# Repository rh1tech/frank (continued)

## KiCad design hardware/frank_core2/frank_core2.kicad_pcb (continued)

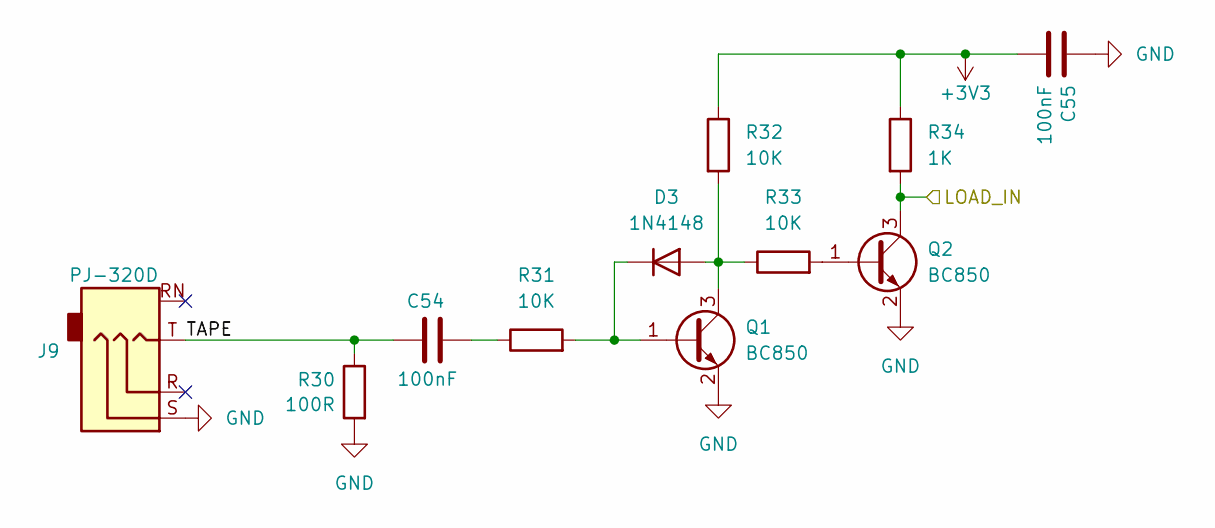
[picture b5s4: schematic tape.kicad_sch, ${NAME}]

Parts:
C54, C55: 100nF; C_0603_1608Metric; LCSC C14663
D3: 1N4148; D_SOD-323; LCSC C2128
J9: PJ-320D; AudioJack_3.5mm_PJ320D_TapeIn; LCSC C431535
Q1, Q2: BC850; SOT-23; LCSC C503377
R30: 100R; R_0603_1608Metric; LCSC C22775
R31, R32, R33: 10K; R_0603_1608Metric; LCSC C2906982
R34: 1K; R_0603_1608Metric; LCSC C21190

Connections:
+3V3: C55.2, R32.1, R34.1; also elsewhere on the board
/RP2350B/GPIO44: Q2.3 (C), R34.2; also elsewhere on the board
/Tape/TAPE: C54.1, J9.T, R30.1
GND: C55.1, J9.S, Q1.2 (E), Q2.2 (E), R30.2; also elsewhere on the board
unnamed: C54.2, R31.1
unnamed: D3.2 (A), Q1.3 (C), R32.2, R33.1
unnamed: D3.1 (K), Q1.1 (B), R31.2
unnamed: Q2.1 (B), R33.2

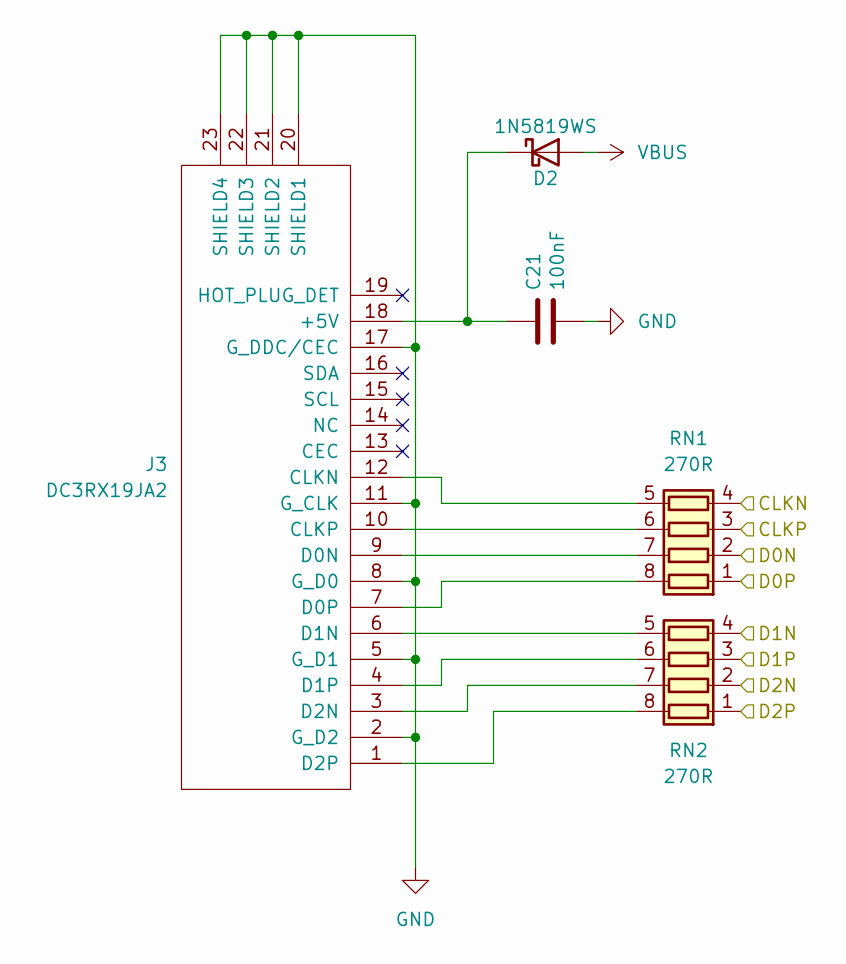
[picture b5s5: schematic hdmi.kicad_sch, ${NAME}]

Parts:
C21: 100nF; C_0603_1608Metric; LCSC C14663
D2: 1N5819WS; D_SOD-323; LCSC C191023
J3: DC3RX19JA2; HDMI_Female
RN1, RN2: 270R; R_Array_4x0603; LCSC C1731063

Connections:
/GPIO12/CLKN: RN1.4 (R4.1); also elsewhere on the board
/GPIO13/CLKP: RN1.3 (R3.1); also elsewhere on the board
/GPIO14/D0N: RN1.2 (R2.1); also elsewhere on the board
/GPIO15/D0P: RN1.1 (R1.1); also elsewhere on the board
/GPIO16/D1N: RN2.4 (R4.1); also elsewhere on the board
/GPIO17/D1P: RN2.3 (R3.1); also elsewhere on the board
/GPIO18/D2N: RN2.2 (R2.1); also elsewhere on the board
/GPIO19/D2P: RN2.1 (R1.1); also elsewhere on the board
GND: C21.2, J3.2 (G_D2), J3.5 (G_D1), J3.8 (G_D0), J3.11 (G_CLK), J3.17 (G_DDC/CEC), J3.20 (SHIELD1), J3.21 (SHIELD2), J3.22 (SHIELD3), J3.23 (SHIELD4); also elsewhere on the board
unnamed: C21.1, D2.1 (K), J3.18 (+5V)
unnamed: J3.12 (CLKN), RN1.5 (R4.2)
unnamed: J3.10 (CLKP), RN1.6 (R3.2)
unnamed: J3.9 (D0N), RN1.7 (R2.2)
unnamed: J3.7 (D0P), RN1.8 (R1.2)
unnamed: J3.6 (D1N), RN2.5 (R4.2)
unnamed: J3.4 (D1P), RN2.6 (R3.2)
unnamed: J3.3 (D2N), RN2.7 (R2.2)
unnamed: J3.1 (D2P), RN2.8 (R1.2)
VBUS: D2.2 (A); also elsewhere on the board

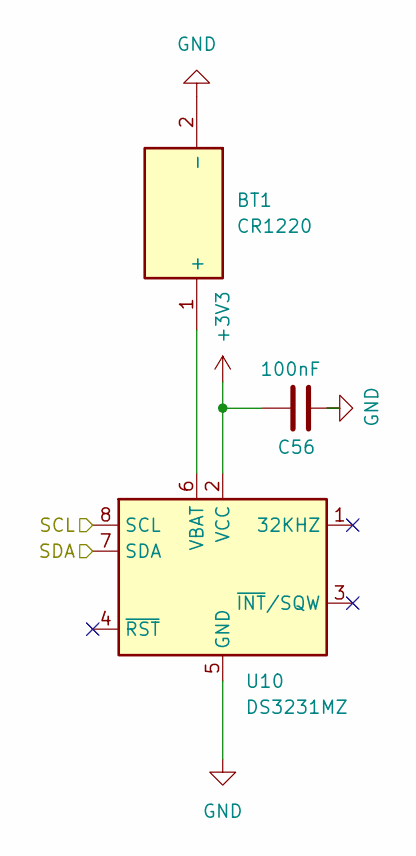
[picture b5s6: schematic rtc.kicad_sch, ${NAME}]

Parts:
BT1: CR1220; Battery_CR1220; Manufacturer_Part_Number 1174; LCSC C5199899
C56: 100nF; C_0603_1608Metric; LCSC C14663
U10: DS3231MZ; SO-8_3.9x4.9mm_P1.27mm; LCSC C107410

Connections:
+3V3: C56.1, U10.2 (VCC); also elsewhere on the board
/GPIO2/SDA: U10.7 (SDA); also elsewhere on the board
/GPIO3/SCL: U10.8 (SCL); also elsewhere on the board
GND: BT1.2 (-), C56.2, U10.5 (GND); also elsewhere on the board
unnamed: BT1.1 (+), U10.6 (VBAT)

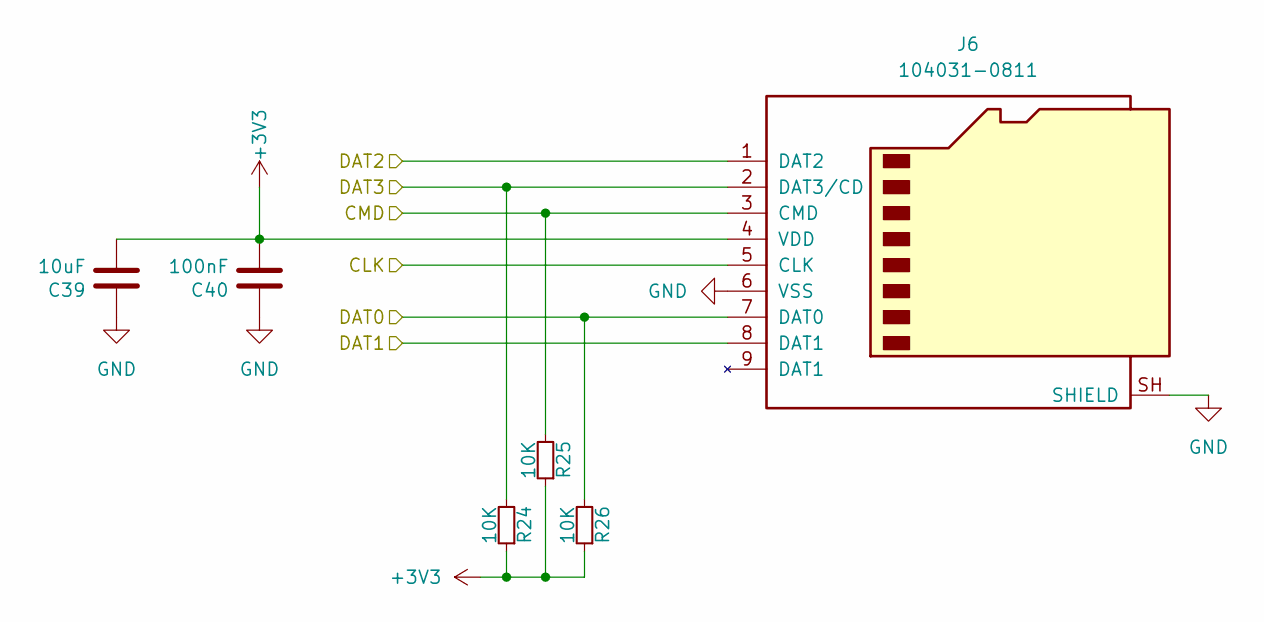
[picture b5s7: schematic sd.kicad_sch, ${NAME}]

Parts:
C39: 10uF; C_0603_1608Metric; LCSC C96446
C40: 100nF; C_0603_1608Metric; LCSC C14663
J6: 104031-0811; MicroSD_SMD_Long; LCSC C585350
R24, R25, R26: 10K; R_0603_1608Metric; LCSC C2906982

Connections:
+3V3: C39.2, C40.2, J6.4 (VDD), R24.1, R25.1, R26.1; also elsewhere on the board
/MicroSD/DAT1: J6.8 (DAT1)
/MicroSD/DAT2: J6.1 (DAT2)
/SD/CDDAT3/GPIO5: J6.2 (DAT3/CD), R24.2; also elsewhere on the board
/SD/CLK/GPIO6: J6.5 (CLK); also elsewhere on the board
/SD/CMD/GPIO7: J6.3 (CMD), R25.2; also elsewhere on the board
/SD/DAT0/GPIO4: J6.7 (DAT0), R26.2; also elsewhere on the board
GND: C39.1, C40.1, J6.6 (VSS), J6.SH (SHIELD); also elsewhere on the board

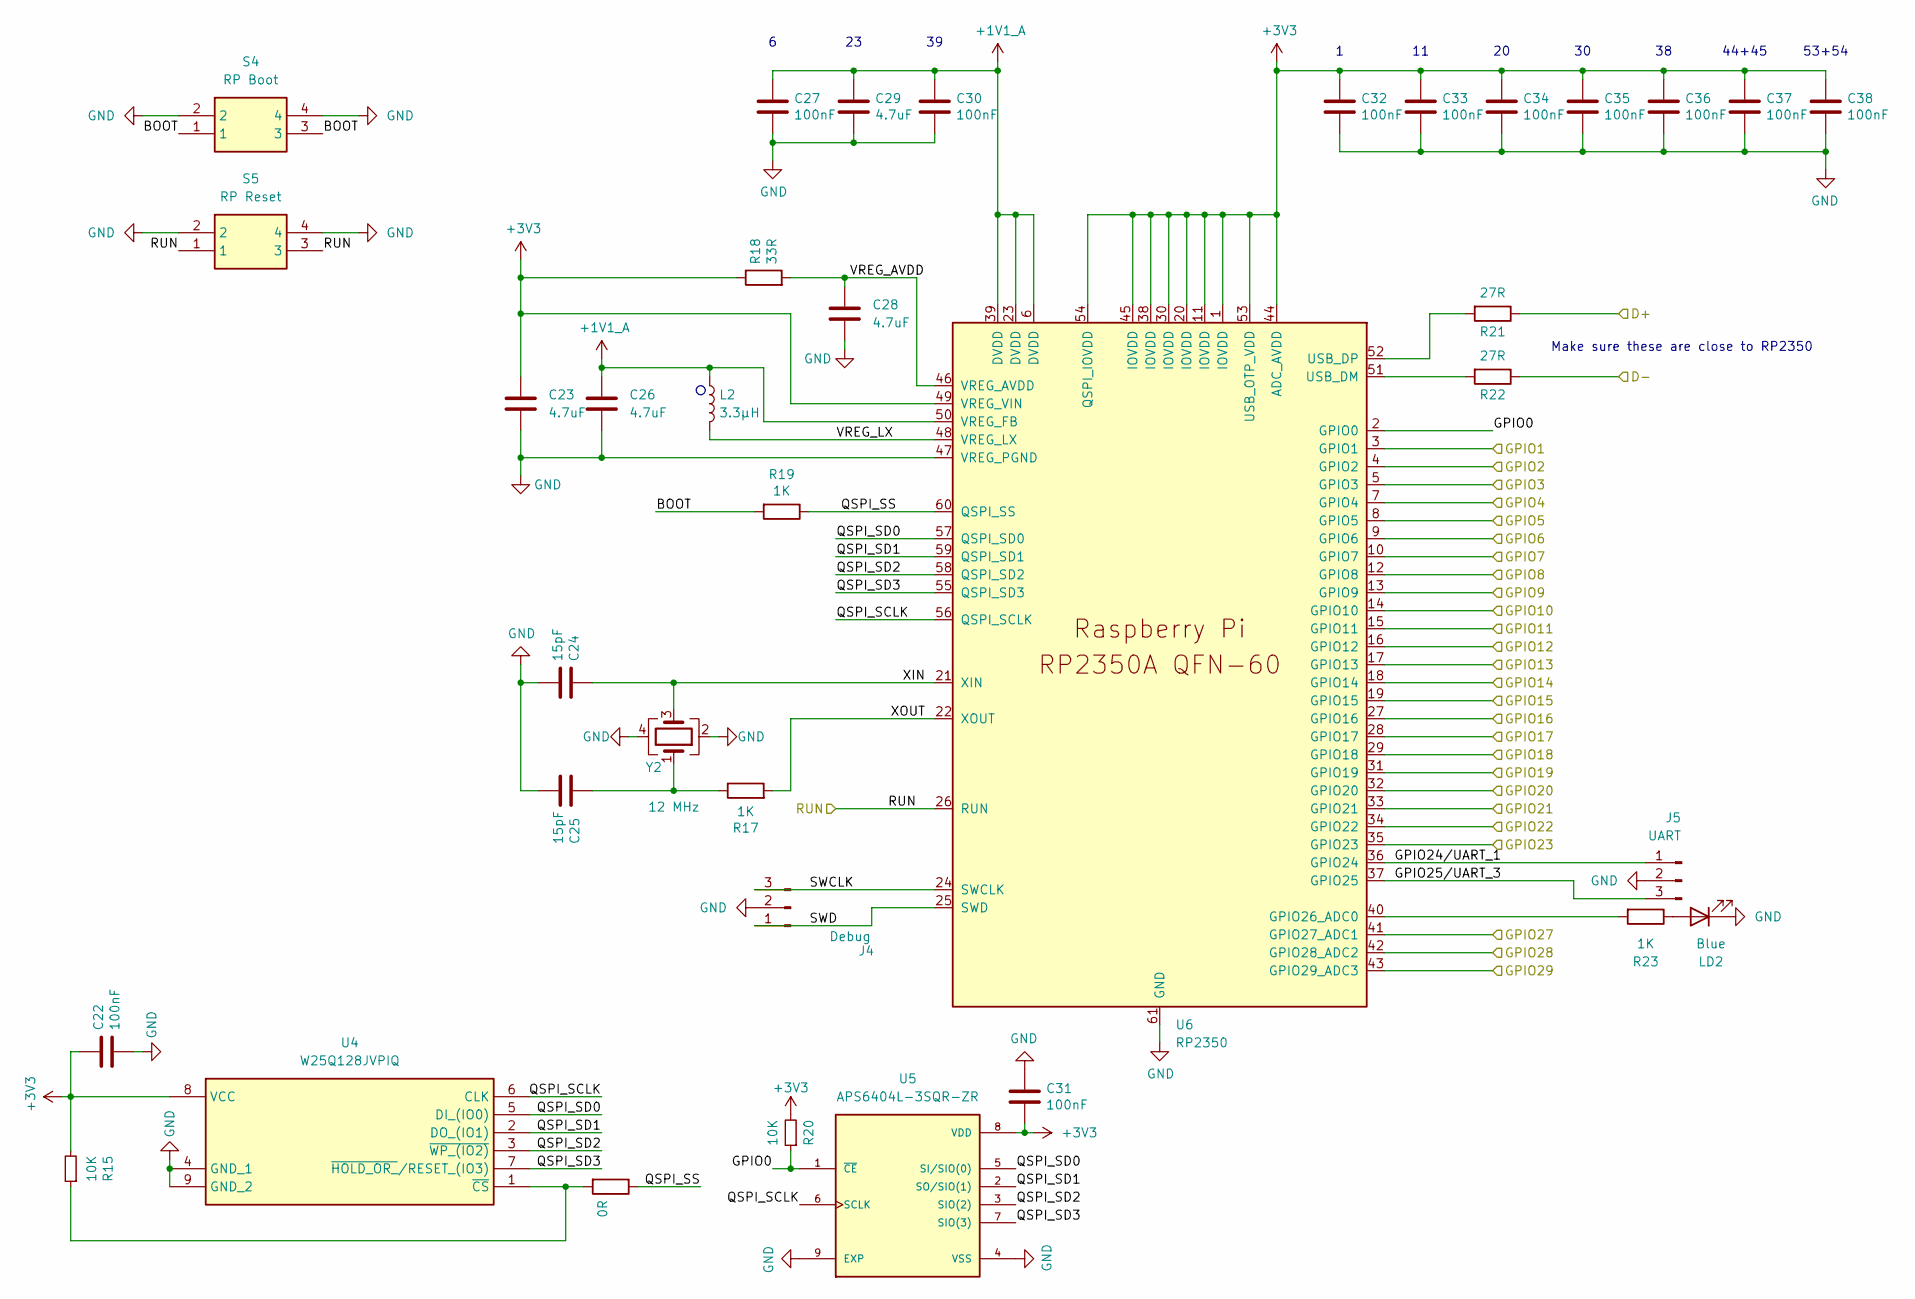
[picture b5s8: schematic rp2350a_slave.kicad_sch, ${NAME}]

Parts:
C22, C27, C30, C31, C32, C33, C34, C35, C36, C37, C38: 100nF; C_0603_1608Metric; LCSC C14663
C23, C26, C28, C29: 4.7uF; C_0603_1608Metric; LCSC C5360844
C24, C25: 15pF; C_0603_1608Metric; LCSC C1644
J4: Debug; JST_SH_1x03_P1.00mm_Vertical; LCSC C160389
J5: UART; JST_SH_1x03_P1.00mm_Vertical; LCSC C160389
L2: 3.3µH; L_AOTA-B201610_2.0x1.6mm; LCSC C98035
LD2: Blue; LED_0603_1608Metric
R15, R20: 10K; R_0603_1608Metric; LCSC C2906982
R16: 0R; R_0603_1608Metric; LCSC C21189
R17, R19, R23: 1K; R_0603_1608Metric; LCSC C21190
R18: 33R; R_0603_1608Metric; LCSC C23140
R21, R22: 27R; R_0603_1608Metric; LCSC C25190
S4: RP Boot; Button_SMD_3x4x2mm; Mouser Part Number 611-KMR221G-LFS; LCSC C36498961
S5: RP Reset; Button_SMD_3x4x2mm; Mouser Part Number 611-KMR221G-LFS; LCSC C36498961
U4: W25Q128JVPIQ; WSON-8-1EP_6x5mm_P1.27mm_EP3.45x4.35mm; Mouser Part Number 454-W25Q128JVPIQ; LCSC C190862
U5: APS6404L-3SQR-ZR; PSON50P200X300X50-9N; PARTREV 2.3; LCSC C3040877
U6: RP2350; QFN-60-1EP_7x7mm_P0.4mm_EP3.4x3.4mm
Y2: 12 MHz; Crystal_SMD_3225-4Pin_3.2x2.5mm; LCSC C9002

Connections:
+1V1_A: C26.1, C27.1, C29.1, C30.1, L2.1, U6.6 (DVDD), U6.23 (DVDD), U6.39 (DVDD), U6.50 (VREG_FB)
+3V3: C22.1, C23.1, C31.2, C32.1, C33.1, C34.1, C35.1, C36.1, C37.1, C38.1, R15.2, R18.1, R20.2, U4.8 (VCC), U5.8 (VDD), U6.1 (IOVDD), U6.11 (IOVDD), U6.20 (IOVDD), U6.30 (IOVDD), U6.38 (IOVDD), U6.44 (ADC_AVDD), U6.45 (IOVDD), U6.49 (VREG_VIN), U6.53 (USB_OTP_VDD), U6.54 (QSPI_IOVDD); also elsewhere on the board
/RP2350A/BOOT: R19.2, S4.1, S4.3
/RP2350A/D+: R21.1; also elsewhere on the board
/RP2350A/D-: R22.1; also elsewhere on the board
/RP2350A/GPIO0: R20.1, U5.1 (~CE), U6.2 (GPIO0)
/RP2350A/GPIO9: U6.13 (GPIO9); also elsewhere on the board
/RP2350A/GPIO24/UART_1: J5.1, U6.36 (GPIO24)
/RP2350A/GPIO25/UART_3: J5.3, U6.37 (GPIO25)
/RP2350A/GPIO27: U6.41 (GPIO27_ADC1)
/RP2350A/GPIO28: U6.42 (GPIO28_ADC2)
/RP2350A/GPIO29: U6.43 (GPIO29_ADC3)
/RP2350A/QSPI_SCLK: U4.6 (CLK), U5.6 (SCLK), U6.56 (QSPI_SCLK)
/RP2350A/QSPI_SD0: U4.5 (DI_(IO0)), U5.5 (SI/SIO(0)), U6.57 (QSPI_SD0)
/RP2350A/QSPI_SD1: U4.2 (DO_(IO1)), U5.2 (SO/SIO(1)), U6.59 (QSPI_SD1)
/RP2350A/QSPI_SD2: U4.3 (~WP_(IO2)), U5.3 (SIO(2)), U6.58 (QSPI_SD2)
/RP2350A/QSPI_SD3: U4.7 (~HOLD_OR_/RESET_(IO3)), U5.7 (SIO(3)), U6.55 (QSPI_SD3)
/RP2350A/QSPI_SS: R16.1, R19.1, U6.60 (QSPI_SS)
/RP2350A/SWCLK: J4.3, U6.24 (SWCLK)
/RP2350A/SWD: J4.1, U6.25 (SWD)
/RP2350A/VREG_AVDD: C28.1, R18.2, U6.46 (VREG_AVDD)
/RP2350A/VREG_LX: L2.2, U6.48 (VREG_LX)
/RP2350A/XIN: C24.1, U6.21 (XIN), Y2.3
/RP2350A/XOUT: R17.2, U6.22 (XOUT)
/RP2350/20B/1A/D0: U6.3 (GPIO1); also elsewhere on the board
/RP2350/21B/2A/D1: U6.4 (GPIO2); also elsewhere on the board
/RP2350/22B/3A/D2: U6.5 (GPIO3); also elsewhere on the board
/RP2350/23B/4A/D3: U6.7 (GPIO4); also elsewhere on the board
/RP2350/24B/5A/D4: U6.8 (GPIO5); also elsewhere on the board
/RP2350/25B/6A/D5: U6.9 (GPIO6); also elsewhere on the board
/RP2350/26B/7A/D6: U6.10 (GPIO7); also elsewhere on the board
/RP2350/27B/8A/D7: U6.12 (GPIO8); also elsewhere on the board
/RP2350/29B/10A/VALID: U6.14 (GPIO10); also elsewhere on the board
/RP2350/30B/11A/D0: U6.15 (GPIO11); also elsewhere on the board
/RP2350/31B/12A/D1: U6.16 (GPIO12); also elsewhere on the board
/RP2350/32B/13A/D2: U6.17 (GPIO13); also elsewhere on the board
/RP2350/33B/14A/D3: U6.18 (GPIO14); also elsewhere on the board
/RP2350/34B/15A/D4: U6.19 (GPIO15); also elsewhere on the board
/RP2350/35B/16A/D5: U6.27 (GPIO16); also elsewhere on the board
/RP2350/36B/17A/D6: U6.28 (GPIO17); also elsewhere on the board
/RP2350/37B/18A/D7: U6.29 (GPIO18); also elsewhere on the board
/RP2350/38B/19A/CLK: U6.31 (GPIO19); also elsewhere on the board
/RP2350/39B/20A/VALID: U6.32 (GPIO20); also elsewhere on the board
/RP2350/40B/21A/FS: U6.33 (GPIO21); also elsewhere on the board
/RP2350/41B/22A/DB_MS: U6.34 (GPIO22); also elsewhere on the board
/RP2350/42B/23A/DB_SM: U6.35 (GPIO23); also elsewhere on the board
/RP2350/43B/RUNA/SR: S5.1, S5.3, U6.26 (RUN); also elsewhere on the board
GND: C22.2, C23.2, C24.2, C25.2, C26.2, C27.2, C28.2, C29.2, C30.2, C31.1, C32.2, C33.2, C34.2, C35.2, C36.2, C37.2, C38.2, J4.2, J5.2, LD2.1 (K), S4.2, S4.4, S5.2, S5.4, U4.4 (GND_1), U4.9 (GND_2), U5.4 (VSS), U5.9 (EXP), U6.47 (VREG_PGND), U6.61 (GND), Y2.2, Y2.4; also elsewhere on the board
unnamed: C25.1, R17.1, Y2.1
unnamed: LD2.2 (A), R23.1
unnamed: R15.1, R16.2, U4.1 (~CS)
unnamed: R23.2, U6.40 (GPIO26_ADC0)
unnamed: R22.2, U6.51 (USB_DM)
unnamed: R21.2, U6.52 (USB_DP)

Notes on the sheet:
44+45
Make sure these are close to RP2350
53+54

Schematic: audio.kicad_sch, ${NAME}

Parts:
C41, C42, C46, C49, C50: 100nF; C_0603_1608Metric; LCSC C14663
C43, C44: 100uF; C_1206_3216Metric; LCSC C7432784
C45, C47, C48: 10uF; C_0603_1608Metric; LCSC C96446
C51, C52: 1uF; C_0603_1608Metric; LCSC C29936
J7: PJ-320D; AudioJack_3.5mm_PJ320D_AudioOut; LCSC C431535
J8: Speaker; JST_GH_1x02_P1.25mm
L3: 330R 2A; L_0805_2012Metric; LCSC C76819
R27, R28: 4.7K; R_0603_1608Metric; LCSC C23162
R29: 10K; R_0603_1608Metric; LCSC C2906982
U7: TLV320DAC3100IRHBR; Mouser Part Number 595-V320DAC3100IRHBR; LCSC C179677
U8: XC6206P182MR-G; Mouser Part Number 865-XC6206P182MR-G; LCSC C347373

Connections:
+1V8: C42.2, C51.2, U7.3 (DVDD), U8.2 (VOUT)
+3V3: C41.1, C45.2, C46.2, C47.2, C49.2, C52.2, R27.2, R28.2, R29.2, U7.2 (IOVDD), U7.17 (AVDD), U7.28 (HPVDD), U8.3 (VIN); also elsewhere on the board
/Audio/+5V_SPK: C48.2, C50.2, L3.1, U7.21 (SPKVDD_1), U7.24 (SPKVDD_2)
/Audio/SPKM: J8.2, U7.19 (SPKM_1), U7.23 (SPKM_2)
/Audio/SPKP: J8.1, U7.22 (SPKP_1), U7.26 (SPKP_2)
/GPIO2/SDA: R28.1, U7.9 (SDA); also elsewhere on the board
/GPIO3/SCL: R27.1, U7.10 (SCL); also elsewhere on the board
/GPIO8/MCLK: U7.8 (MCLK); also elsewhere on the board
/GPIO9/BCLK: U7.7 (BCLK); also elsewhere on the board
/GPIO10/WCLK: U7.6 (WCLK); also elsewhere on the board
/GPIO11/DIN: U7.5 (DIN); also elsewhere on the board
GND: C41.2, C42.1, C45.1, C46.1, C47.1, C48.1, C49.1, C50.1, C51.1, C52.1, J7.S, U7.1 (IOVSS), U7.16 (AVSS), U7.18 (DVSS), U7.20 (SPKVSS_1), U7.25 (SPKVSS_2), U7.29 (HPVSS), U7.33 (EP), U8.1 (VSS); also elsewhere on the board
unnamed: C43.1, J7.R
unnamed: C44.1, J7.T
unnamed: C44.2, U7.27 (HPL)
unnamed: C43.2, U7.30 (HPR)
unnamed: R29.1, U7.31 (~RESET)
VBUS: L3.2; also elsewhere on the board

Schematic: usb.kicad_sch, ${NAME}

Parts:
C57, C58, C61, C62, C68, C70, C72: 100nF; C_0603_1608Metric; LCSC C14663
C59, C60: 100uF; C_1206_3216Metric; LCSC C7432784
C63, C64, C65, C66, C67, C69, C71, C73, C75, C76, C77: 10uF; C_0603_1608Metric; LCSC C96446
C74: 1uF; C_0603_1608Metric; LCSC C29936
C78, C79: 12pF; C_0603_1608Metric; LCSC C38523
C80: 22pF; C_0603_1608Metric; LCSC C1653
J10, J11: 676430910; USB_A_Short; LCSC C2798029
J12, J13: USB4215-03-A; USB_C_Receptacle; LCSC C37616412
JP1: USB Debug; SolderJumper-2_P1.3mm_Open_RoundedPad1.0x1.5mm
L4: 330R 2A; L_0805_2012Metric; LCSC C76819
L5: 2.2uH; L_Cenker_CKCS3015; LCSC C167747
LD3: Green; LED_0603_1608Metric; LCSC C965804
R35, R36, R37, R38: 5.1K; R_0603_1608Metric; LCSC C23186
R39: 300K; R_0603_1608Metric; LCSC C23024
R40, R42, R43, R45, R49: 100K; R_0603_1608Metric; LCSC C25803
R41: 1M; R_0603_1608Metric; LCSC C22935; not fitted
R44, R47: 1K; R_0603_1608Metric; LCSC C21190
R46: 10K; R_0603_1608Metric; LCSC C2906982
R48: 4.7K; R_0603_1608Metric; LCSC C23162; not fitted
R50: 22K; R_0603_1608Metric; LCSC C31850
S6: SS12D00; Switch_Slide_SS12D00; Mouser Part Number 611-SK12D07VG3NS
S7: SK12D07VG3NS; Switch_Slide_SK12D07VG3NS_PWR; Mouser Part Number 611-SK12D07VG3NS; LCSC C431547
U11, U12, U13, U14: TPD4S012DRYR; Mouser Part Number 595-TPD4S012DRYR; LCSC C96506
U15, U16: CH217K; SOT-23-6; LCSC C7462749
U17: TPS2116DRL; SOT-583-8; LCSC C3235557
U18: AO3401A; SOT-23-3L_AOS; LCSC C15127
U19: TS3USB221RSER; UQFN-10; LCSC C130085
U20: SY8089AAAC; SOT-23-5; LCSC C78988
U21: CH334F; QFN-24-1EP_4x4mm_P0.5mm_EP2.7x2.7mm; LCSC C5187527
Y3: 12 MHz; Crystal_SMD_3225-4Pin_3.2x2.5mm; LCSC C9002

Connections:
+3V3: C70.2, C75.1, C76.1, C80.1, JP1.1 (A), L5.1, R44.2, R49.1, S6.2, U19.10 (VCC); also elsewhere on the board
/RP2350A/D+: J13.6 (DP1), J13.8 (DP2), U14.1 (D+); also elsewhere on the board
/RP2350A/D-: J13.5 (DN2), J13.7 (DN1), U14.2 (D-_); also elsewhere on the board
/RP2350B/D+: U19.8 (D+); also elsewhere on the board
/RP2350B/D-: U19.7 (D-); also elsewhere on the board
/USB/+5V_BUCK: C69.1, C71.1, C72.1, L4.2, U20.1 (EN), U20.4 (IN)
/USB/D2+: J12.6 (DP1), J12.8 (DP2), U13.1 (D+), U19.1 (1D+)
/USB/D2-: J12.5 (DN2), J12.7 (DN1), U13.2 (D-_), U19.2 (1D-)
/USB/DH+: U19.3 (2D+), U21.15 (DPU+)
/USB/DH-: U19.4 (2D-), U21.14 (DMU-)
/USB/DS1+: J10.3 (D+), U11.1 (D+), U21.12 (DP1+)
/USB/DS1-: J10.2 (D-), U11.2 (D-_), U21.11 (DM1-)
/USB/DS2+: J11.3 (D+), U12.1 (D+), U21.10 (DP2+)
/USB/DS2-: J11.2 (D-), U12.2 (D-_), U21.9 (DM2-)
/USB/OVCUR: U15.3 (FLAG#), U16.3 (FLAG#), U21.1 (~OVCUR)
/USB/PWREN: U15.4 (EN#), U16.4 (EN#), U21.24 (~PWREN)
/USB/S: JP1.2 (B), R46.2, S6.3, U19.9 (S)
/USB/ST: R41.2, U17.8 (ST)
/USB/VBUS_IN: C67.1, C68.2, R45.2, U17.2 (VOUT), U17.7 (VOUT), U18.2 (S)
/USB/VBUS_IN1: C61.2, C65.2, J13.2 (VBUS), J13.11 (VBUS), R39.2, U14.6 (VBUS), U17.3 (VIN1), U17.5 (MODE)
/USB/VBUS_IN2: C62.2, C66.2, J12.2 (VBUS), J12.11 (VBUS), U13.6 (VBUS), U17.6 (VIN2)
/USB/VBUS_P1: C57.1, C59.1, J10.1 (VBUS), U11.6 (VBUS), U15.1 (VOUT)
/USB/VBUS_P2: C58.1, C60.1, J11.1 (VBUS), U12.6 (VBUS), U16.1 (VOUT)
/USB/VDD33: C73.2, C74.2, U21.20 (VDD33_{LDO})
/USB/XTAL_N: C78.1, U21.3 (XO), Y3.3
/USB/XTAL_P: C79.1, U21.4 (XI), Y3.1
GND: C57.2, C58.2, C59.2, C60.2, C61.1, C62.1, C63.1, C64.1, C65.1, C66.1, C67.2, C69.2, C70.1, C71.2, C72.2, C73.1, C74.1, C75.2, C76.2, C77.1, C78.2, C79.2, J10.4 (GND), J10.5 (Shield), J11.4 (GND), J11.5 (Shield), J12.1 (GND), J12.12 (GND), J12.13 (SHIELD), J13.1 (GND), J13.12 (GND), J13.13 (SHIELD), LD3.1 (K), R35.1, R36.1, R37.1, R38.1, R40.1, R42.1, R43.1, R46.1, R48.2, R50.2, S7.2, U11.4 (GND), U12.4 (GND), U13.4 (GND), U14.4 (GND), U15.2 (GND), U16.2 (GND), U17.1 (GND), U19.5 (GND), U19.6 (~OE), U20.2 (GND), U21.25 (GND), Y3.2, Y3.4; also elsewhere on the board
unnamed: J12.4 (CC1), R35.2
unnamed: J12.10 (CC2), R36.2
unnamed: J13.4 (CC1), R37.2
unnamed: J13.10 (CC2), R38.2
unnamed: LD3.2 (A), R44.1
unnamed: R47.2, S7.3
unnamed: R42.2, U15.5 (ISET)
unnamed: R43.2, U16.5 (ISET)
unnamed: R39.1, R40.2, R41.1, U17.4 (PR1)
unnamed: C68.1, R45.1, R47.1, U18.1 (G)
unnamed: C80.2, R49.2, R50.1, U20.5 (FB)
unnamed: L5.2, U20.3 (LX)
unnamed: R48.1, U21.18 (PSELF)
VBUS: C63.2, C64.2, C77.2, L4.1, U15.6 (VIN), U16.6 (VIN), U18.3 (D), U21.19 (V5); also elsewhere on the board

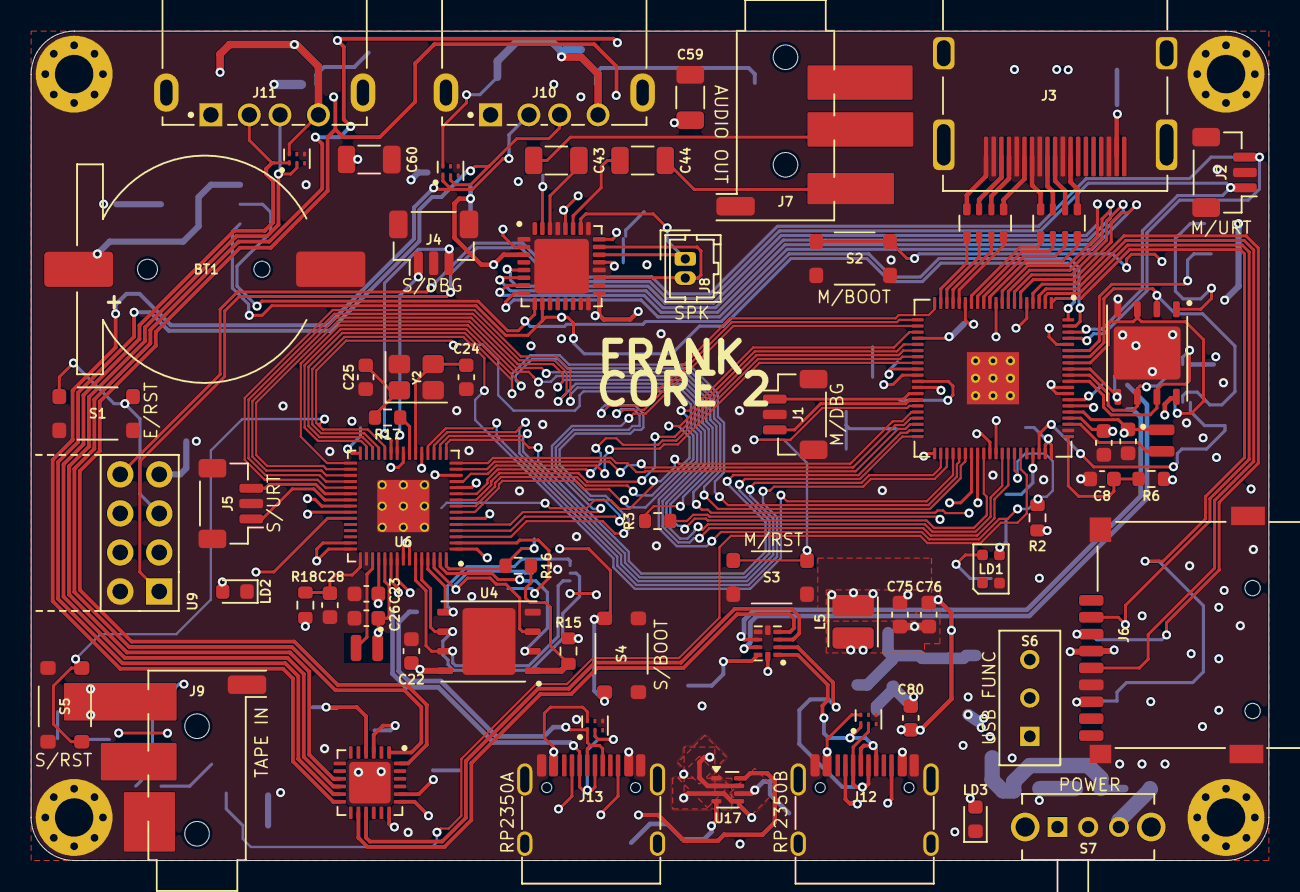
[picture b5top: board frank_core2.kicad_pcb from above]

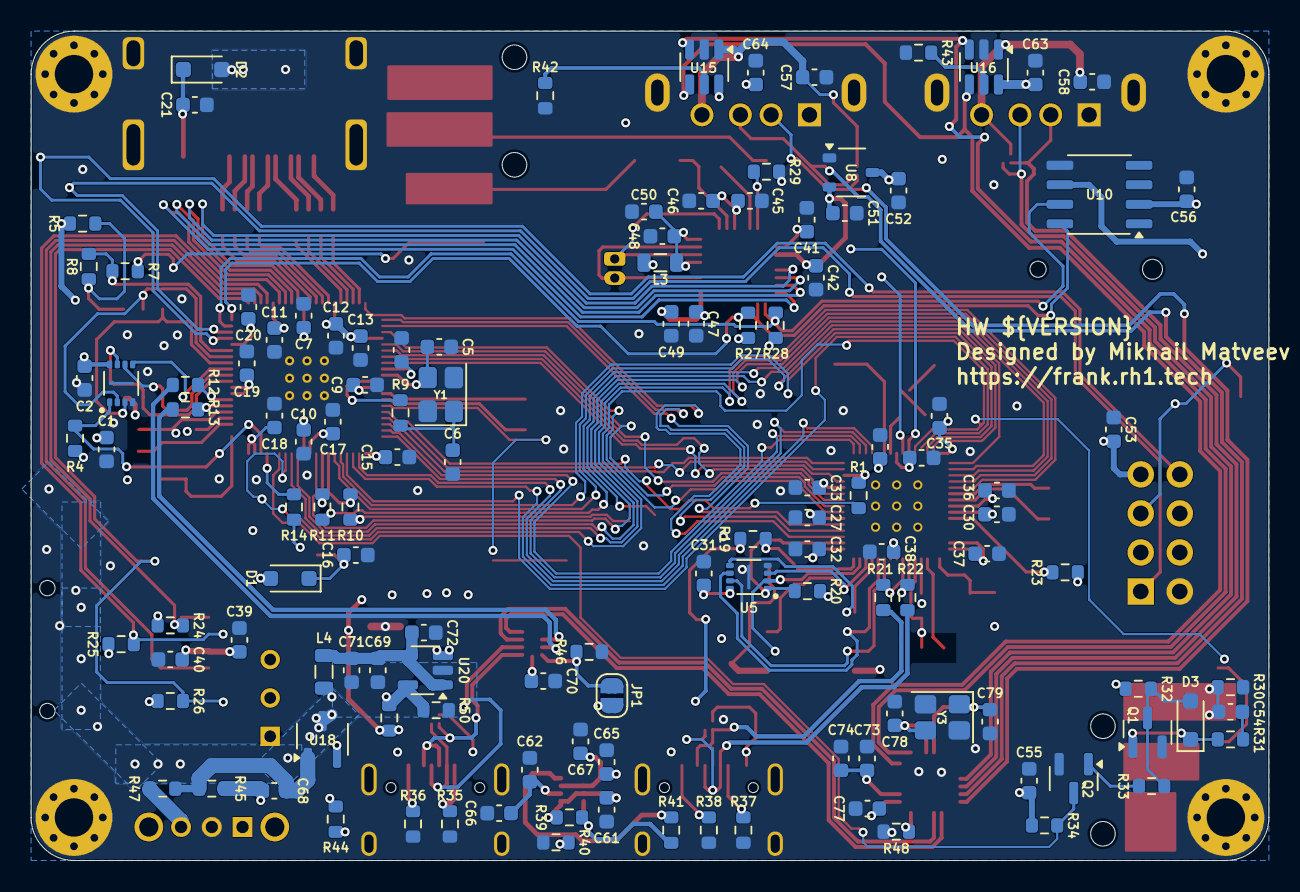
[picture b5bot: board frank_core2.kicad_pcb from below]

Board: 4 copper layers, 80.6 x 54.0 mm, 195 parts (125 on the bottom side), 161 nets.
